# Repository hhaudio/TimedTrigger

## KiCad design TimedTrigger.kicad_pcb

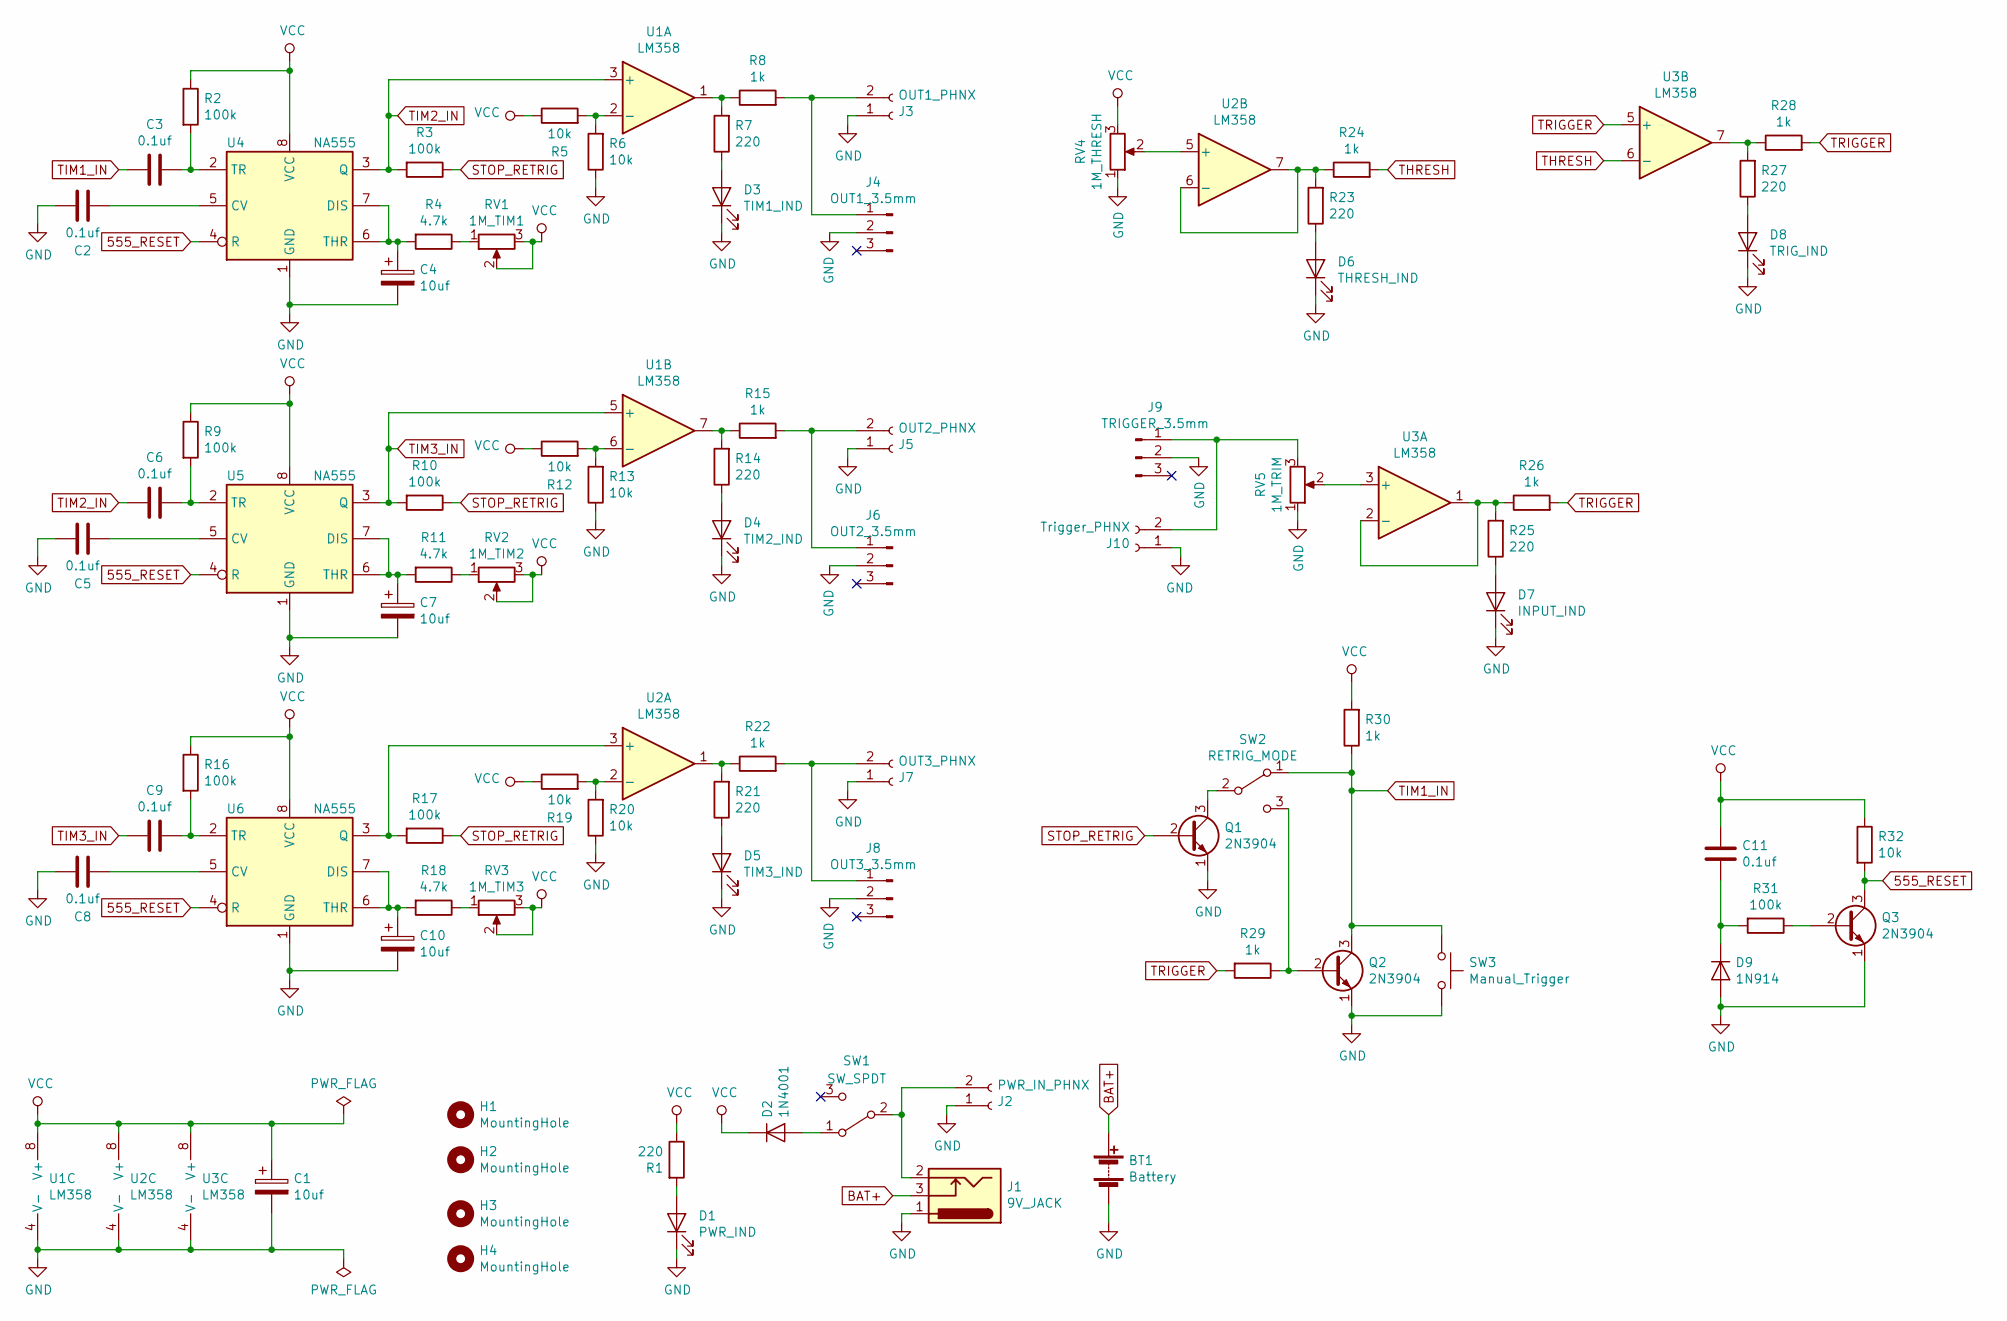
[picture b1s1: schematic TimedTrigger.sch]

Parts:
BT1: Battery; 9V_Clip_Nicer_Fixed
C1, C4, C7, C10: 10uf; CP_Radial_D6.3mm_P2.50mm
C2, C3, C5, C6, C8, C9, C11: 0.1uf; C_Disc_D3.0mm_W2.0mm_P2.50mm
D1: PWR_IND; LED_D5.0mm
D2: 1N4001; D_DO-41_SOD81_P7.62mm_Horizontal
D3: TIM1_IND; LED_D5.0mm
D4: TIM2_IND; LED_D5.0mm
D5: TIM3_IND; LED_D5.0mm
D6: THRESH_IND; LED_D5.0mm
D7: INPUT_IND; LED_D5.0mm
D8: TRIG_IND; LED_D5.0mm
D9: 1N914; D_DO-35_SOD27_P7.62mm_Horizontal
H1, H2, H3, H4: MountingHole; M3_MOUNT
J1: 9V_JACK; BarrelJack_Horizontal
J2: PWR_IN_PHNX; PhoenixContact_MC_1,5_2-G-3.81_1x02_P3.81mm_Horizontal
J3: OUT1_PHNX; PhoenixContact_MC_1,5_2-G-3.81_1x02_P3.81mm_Horizontal
J4: OUT1_3.5mm; EuroJack_MonoSW_THT
J5: OUT2_PHNX; PhoenixContact_MC_1,5_2-G-3.81_1x02_P3.81mm_Horizontal
J6: OUT2_3.5mm; EuroJack_MonoSW_THT
J7: OUT3_PHNX; PhoenixContact_MC_1,5_2-G-3.81_1x02_P3.81mm_Horizontal
J8: OUT3_3.5mm; EuroJack_MonoSW_THT
J9: TRIGGER_3.5mm; EuroJack_MonoSW_THT
J10: Trigger_PHNX; PhoenixContact_MC_1,5_2-G-3.81_1x02_P3.81mm_Horizontal
Q1, Q2, Q3: 2N3904; TO-92_Inline_Wide
R1, R7, R14, R21, R23, R25, R27: 220; R_THT_P7.62
R2, R3, R9, R10, R16, R17, R31: 100k; R_THT_P7.62
R4, R11, R18: 4.7k; R_THT_P7.62
R5, R6, R12, R13, R19, R20, R32: 10k; R_THT_P7.62
R8, R15, R22, R24, R26, R28, R29, R30: 1k; R_THT_P7.62
RV1: 1M_TIM1; PTV09_PT6_Stacked
RV2: 1M_TIM2; PTV09_PT6_Stacked
RV3: 1M_TIM3; PTV09_PT6_Stacked
RV4: 1M_THRESH; PTV09_PT6_Stacked
RV5: 1M_TRIM; PTV09_PT6_Stacked
SW1: SW_SPDT; Tayda_Slide_SPDT
SW2: RETRIG_MODE; Tayda_Slide_SPDT
SW3: Manual_Trigger; SW_PUSH_6mm
U1, U2: LM358; DIP-8_W7.62mm
U3: LM358
U4, U5, U6: NA555; DIP-8_W7.62mm

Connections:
555_RESET: Q3.3 (C), R32.2, U4.4 (R), U5.4 (R), U6.4 (R)
BAT+: BT1.1 (+), J1.3
GND: BT1.2 (-), C1.2, C2.2, C4.2, C5.2, C7.2, C8.2, C10.2, D1.1 (K), D3.1 (K), D4.1 (K), D5.1 (K), D6.1 (K), D7.1 (K), D8.1 (K), D9.2 (A), J1.1, J2.1, J3.1, J4.2, J5.1, J6.2, J7.1, J8.2, J9.2, J10.1, Q1.1 (E), Q2.1 (E), Q3.1 (E), R6.1, R13.1, R20.1, RV4.1, RV5.1, SW3.2, U1.4 (V-), U2.4 (V-), U3.4 (V-), U4.1 (GND), U5.1 (GND), U6.1 (GND)
unnamed: C2.1, U4.5 (CV)
unnamed: C3.1, R2.2, U4.2 (TR)
unnamed: C4.1, R4.2, U4.6 (THR), U4.7 (DIS)
unnamed: C5.1, U5.5 (CV)
unnamed: C6.1, R9.2, U5.2 (TR)
unnamed: C7.1, R11.2, U5.6 (THR), U5.7 (DIS)
unnamed: C8.1, U6.5 (CV)
unnamed: C9.1, R16.2, U6.2 (TR)
unnamed: C10.1, R18.2, U6.6 (THR), U6.7 (DIS)
unnamed: C11.2, D9.1 (K), R31.2
unnamed: D1.2 (A), R1.2
unnamed: D2.2 (A), SW1.1 (A)
unnamed: D3.2 (A), R7.1
unnamed: D4.2 (A), R14.1
unnamed: D5.2 (A), R21.1
unnamed: D6.2 (A), R23.1
unnamed: D7.2 (A), R25.1
unnamed: D8.2 (A), R27.1
unnamed: J1.2, J2.2, SW1.2 (B)
unnamed: J3.2, J4.1, R8.2
unnamed: J5.2, J6.1, R15.2
unnamed: J7.2, J8.1, R22.2
unnamed: J9.1, J10.2, RV5.3
unnamed: Q1.3 (C), SW2.2 (B)
unnamed: Q2.2 (B), R29.1, SW2.3 (C)
unnamed: Q3.2 (B), R31.1
unnamed: R4.1, RV1.1
unnamed: R5.2, R6.2, U1.2 (-)
unnamed: R7.2, R8.1, U1.1
unnamed: R11.1, RV2.1
unnamed: R12.2, R13.2, U1.6 (-)
unnamed: R14.2, R15.1, U1.7
unnamed: R17.2, U2.3 (+), U6.3 (Q)
unnamed: R18.1, RV3.1
unnamed: R19.2, R20.2, U2.2 (-)
unnamed: R21.2, R22.1, U2.1
unnamed: R23.2, R24.1, U2.6 (-), U2.7
unnamed: R25.2, R26.1, U3.1, U3.2 (-)
unnamed: R27.2, R28.1, U3.7
unnamed: RV4.2, U2.5 (+)
unnamed: RV5.2, U3.3 (+)
STOP_RETRIG: Q1.2 (B), R3.1, R10.1, R17.1
THRESH: R24.2, U3.6 (-)
TIM1_IN: C3.2, Q2.3 (C), R30.1, SW2.1 (A), SW3.1
TIM2_IN: C6.2, R3.2, U1.3 (+), U4.3 (Q)
TIM3_IN: C9.2, R10.2, U1.5 (+), U5.3 (Q)
TRIGGER: R26.2, R28.2, R29.2, U3.5 (+)
VCC: C1.1, C11.1, D2.1 (K), R1.1, R2.1, R5.1, R9.1, R12.1, R16.1, R19.1, R30.2, R32.1, RV1.2, RV1.3, RV2.2, RV2.3, RV3.2, RV3.3, RV4.3, U1.8 (V+), U2.8 (V+), U3.8 (V+), U4.8 (VCC), U5.8 (VCC), U6.8 (VCC)

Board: 2 copper layers, 84 parts (1 on the bottom side), 51 nets, no tracks yet.

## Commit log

2019-11-16 Made schematic for timed trigger
2019-11-16 added components
2019-11-16 Started laying out components
